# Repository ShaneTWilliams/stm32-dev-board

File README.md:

# stm32-dev-board
### ***A small-footprint, custom development PCB for the STM32 platform***

* This board's MCU is an STM32F072CBT6, meaning it is a higher-end 48-pin LQFP chip with 128kB of flash and an ARM Cortex-M0 core.

* The board supports CANbus, LINbus, I<sup>2</sup>C, SPI, USB,  and UART. Flashing can be achieved through an ST-LINK external flasher using the SWD protocol.

* The board is powered through a Micro-USB port and draws very little current. Power conversion occurs through a 5~3.3V linear regulator.

* The board has a 32.768kHz clock for RTC capabilities as well as an 8MHz system clock. It also features an indicator LED and a reset button.

* The footprint of the board is 19x52 mm and its 2.54 mm pitch headers allow it to be used with standard breadboards.

### Images ###

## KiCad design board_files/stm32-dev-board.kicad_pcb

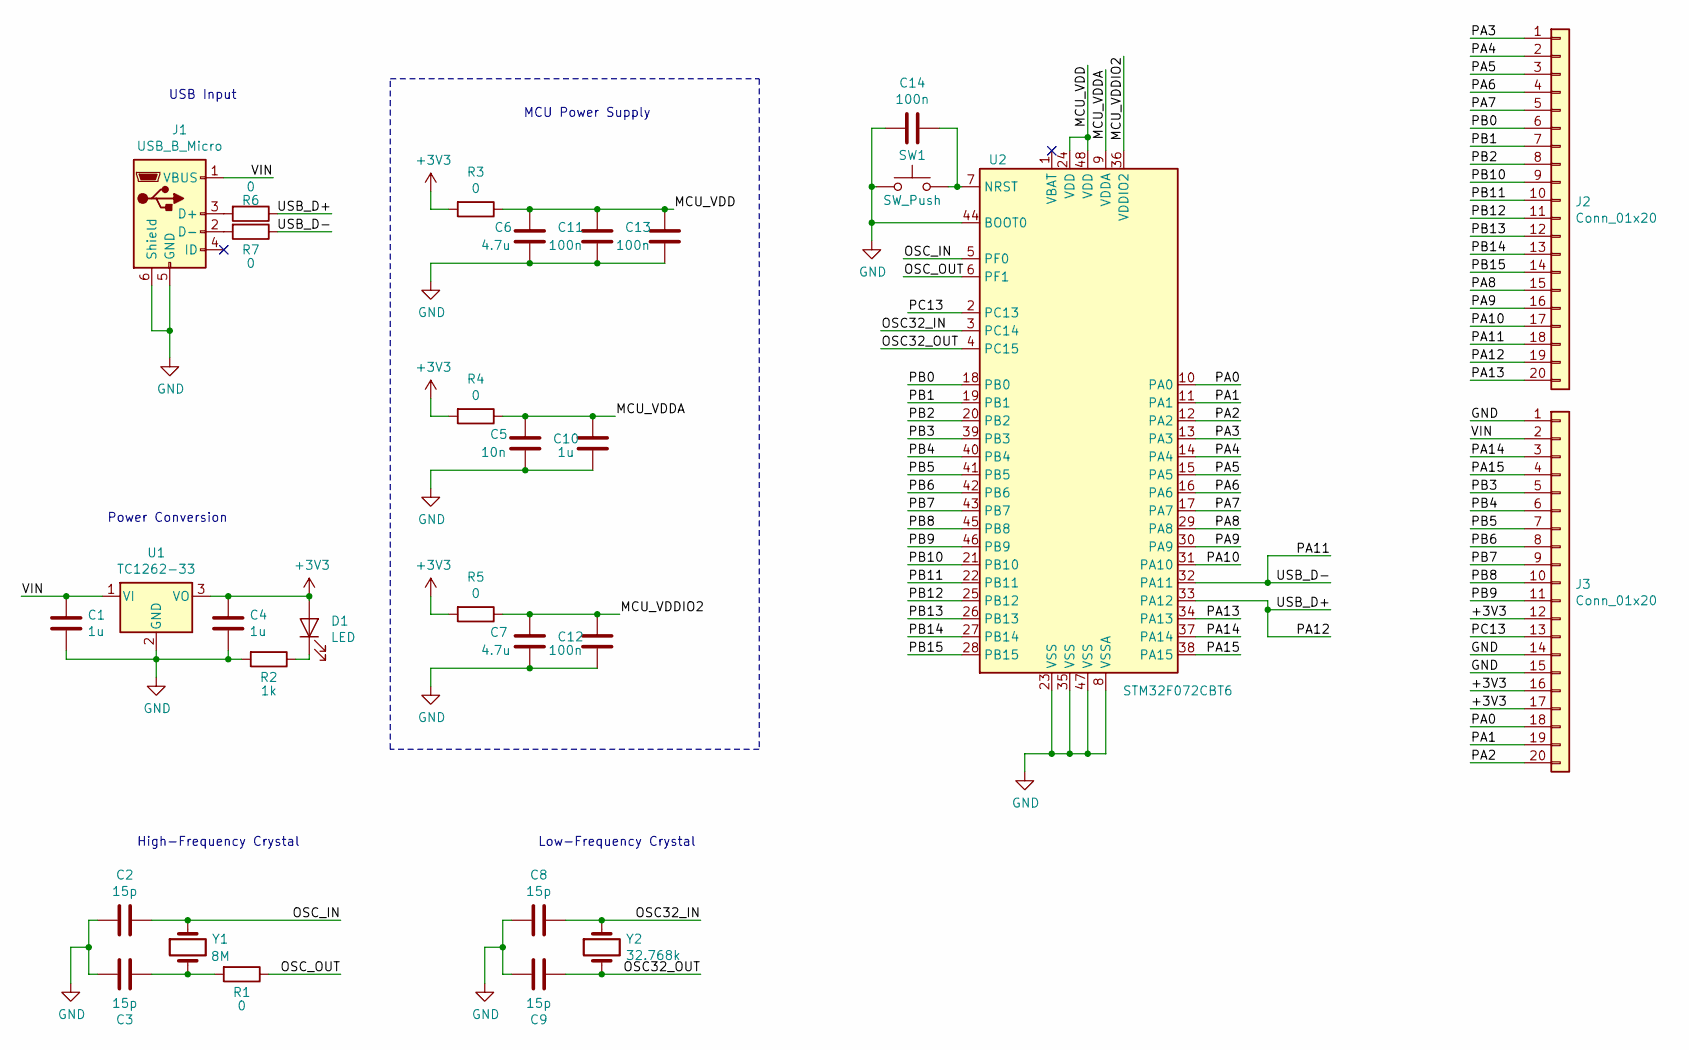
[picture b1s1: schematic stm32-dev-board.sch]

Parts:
C1, C4, C10: 1u; C_0805_2012Metric_Pad1.15x1.40mm_HandSolder
C2, C3, C8, C9: 15p; C_0805_2012Metric_Pad1.15x1.40mm_HandSolder
C5: 10n; C_0805_2012Metric_Pad1.15x1.40mm_HandSolder
C6, C7: 4.7u; C_0805_2012Metric_Pad1.15x1.40mm_HandSolder
C11, C12, C13, C14: 100n; C_0805_2012Metric_Pad1.15x1.40mm_HandSolder
D1: LED; LED_0805_2012Metric_Pad1.15x1.40mm_HandSolder
J1: USB_B_Micro; USB_Micro-B_Amphenol_10103594-0001LF_Horizontal
J2, J3: Conn_01x20; PinHeader_1x20_P2.54mm_Vertical
R1, R3, R4, R5, R6, R7: 0; R_0805_2012Metric_Pad1.15x1.40mm_HandSolder
R2: 1k; R_0805_2012Metric_Pad1.15x1.40mm_HandSolder
SW1: SW_Push; PTS645SM43SMTR92_Switch
U1: TC1262-33; SOT-223
U2: STM32F072CBT6; LQFP-48_7x7mm_P0.5mm
Y1: 8M; 2-SMD_Crystal
Y2: 32.768k; FC-135

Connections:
+3V3: C4.2, D1.2 (A), J3.12, J3.16, J3.17, R3.2, R4.2, R5.2, U1.3 (VO)
/MCU_VDD: C6.1, C11.1, C13.1, R3.1, U2.24 (VDD), U2.48 (VDD)
/MCU_VDDA: C5.1, C10.1, R4.1, U2.9 (VDDA)
/MCU_VDDIO2: C7.1, C12.1, R5.1, U2.36 (VDDIO2)
/OSC32_IN: C8.1, U2.3 (PC14), Y2.1
/OSC32_OUT: C9.2, U2.4 (PC15), Y2.2
/OSC_IN: C2.1, U2.5 (PF0), Y1.1
/OSC_OUT: R1.1, U2.6 (PF1)
/PA0: J3.18, U2.10 (PA0)
/PA1: J3.19, U2.11 (PA1)
/PA2: J3.20, U2.12 (PA2)
/PA3: J2.1, U2.13 (PA3)
/PA4: J2.2, U2.14 (PA4)
/PA5: J2.3, U2.15 (PA5)
/PA6: J2.4, U2.16 (PA6)
/PA7: J2.5, U2.17 (PA7)
/PA8: J2.15, U2.29 (PA8)
/PA9: J2.16, U2.30 (PA9)
/PA10: J2.17, U2.31 (PA10)
/PA11: J2.18, R7.1, U2.32 (PA11)
/PA12: J2.19, R6.1, U2.33 (PA12)
/PA13: J2.20, U2.34 (PA13)
/PA14: J3.3, U2.37 (PA14)
/PA15: J3.4, U2.38 (PA15)
/PB0: J2.6, U2.18 (PB0)
/PB1: J2.7, U2.19 (PB1)
/PB2: J2.8, U2.20 (PB2)
/PB3: J3.5, U2.39 (PB3)
/PB4: J3.6, U2.40 (PB4)
/PB5: J3.7, U2.41 (PB5)
/PB6: J3.8, U2.42 (PB6)
/PB7: J3.9, U2.43 (PB7)
/PB8: J3.10, U2.45 (PB8)
/PB9: J3.11, U2.46 (PB9)
/PB10: J2.9, U2.21 (PB10)
/PB11: J2.10, U2.22 (PB11)
/PB12: J2.11, U2.25 (PB12)
/PB13: J2.12, U2.26 (PB13)
/PB14: J2.13, U2.27 (PB14)
/PB15: J2.14, U2.28 (PB15)
/PC13: J3.13, U2.2 (PC13)
/VIN: C1.2, J1.1 (VBUS), J3.2, U1.1 (VI)
GND: C1.1, C2.2, C3.1, C4.1, C5.2, C6.2, C7.2, C8.2, C9.1, C10.2, C11.2, C12.2, C13.2, C14.2, J1.5 (GND), J1.6 (Shield), J3.1, J3.14, J3.15, R2.2, SW1.1, U1.2 (GND), U1.4, U2.8 (VSSA), U2.23 (VSS), U2.35 (VSS), U2.44 (BOOT0), U2.47 (VSS)
unnamed: C3.2, R1.2, Y1.2
unnamed: C14.1, SW1.2, U2.7 (NRST)
unnamed: D1.1 (K), R2.1
unnamed: J1.2 (D-), R7.2
unnamed: J1.3 (D+), R6.2

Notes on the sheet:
High-Frequency Crystal
Low-Frequency Crystal
USB Input
Power Conversion
MCU Power Supply

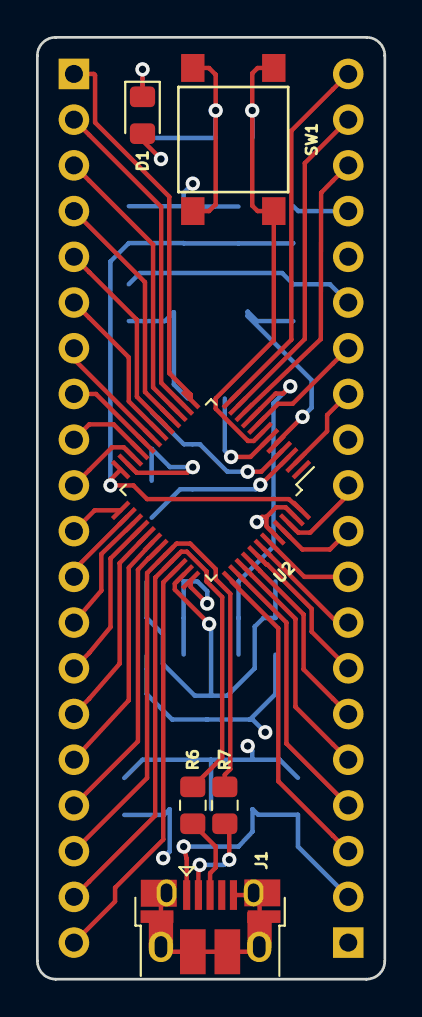
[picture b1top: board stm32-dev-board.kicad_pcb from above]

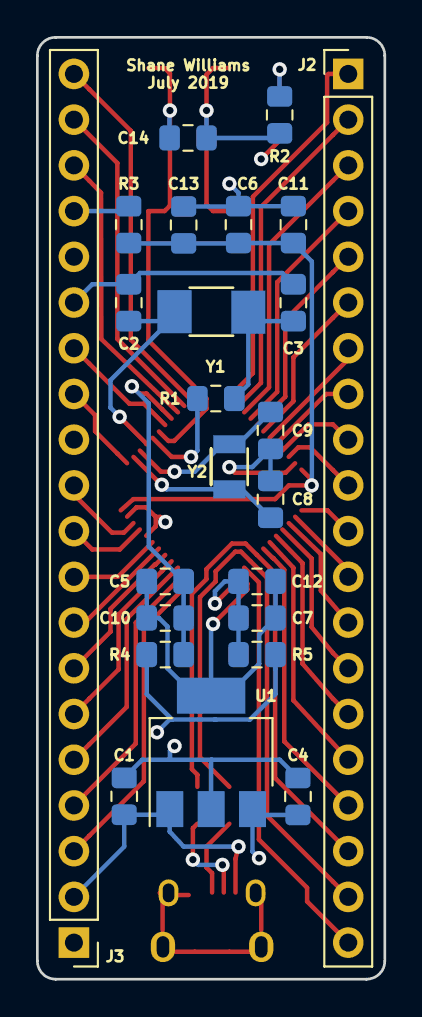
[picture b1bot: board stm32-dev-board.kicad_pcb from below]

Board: 4 copper layers, 19.3 x 52.3 mm, 30 parts (24 on the bottom side), 48 nets.

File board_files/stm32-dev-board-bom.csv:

"Id";"Designator";"Package";"Quantity";"Designation";"Supplier and ref";
1;"C1,C4,C10";"C_0805_2012Metric_Pad1.15x1.40mm_HandSolder";3;"1u";;;
2;"C2,C3,C8,C9";"C_0805_2012Metric_Pad1.15x1.40mm_HandSolder";4;"15p";;;
3;"C5";"C_0805_2012Metric_Pad1.15x1.40mm_HandSolder";1;"10n";;;
4;"C6,C7";"C_0805_2012Metric_Pad1.15x1.40mm_HandSolder";2;"4.7u";;;
5;"C11,C12,C13,C14";"C_0805_2012Metric_Pad1.15x1.40mm_HandSolder";4;"100n";;;
6;"D1";"LED_0805_2012Metric_Pad1.15x1.40mm_HandSolder";1;"LED";;;
7;"J1";"USB_Micro-B_Amphenol_10103594-0001LF_Horizontal";1;"USB_B_Micro";;;
8;"J2,J3";"PinHeader_1x20_P2.54mm_Vertical";2;"Conn_01x20";;;
9;"R1,R3,R4,R5,R6,R7";"R_0805_2012Metric_Pad1.15x1.40mm_HandSolder";6;"0";;;
10;"R2";"R_0805_2012Metric_Pad1.15x1.40mm_HandSolder";1;"1k";;;
11;"SW1";"PTS645SM43SMTR92_Switch";1;"SW_Push";;;
12;"U1";"SOT-223";1;"TC1262-33";;;
13;"U2";"LQFP-48_7x7mm_P0.5mm";1;"STM32F072CBT6";;;
14;"Y1";"2-SMD_Crystal";1;"8M";;;
15;"Y2";"FC-135";1;"32.768k";;;

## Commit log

2019-08-05 Add .gitignore
2019-08-05 Add board files
2019-08-19 Add schematic metadata
